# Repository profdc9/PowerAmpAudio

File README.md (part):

# Modified C300 Amplifier

This is a PCB layout by Daniel Marks based on Michael Chua's C300 amplifier which can be found at:

https://www.ampslab.com/c300.htm

This is a project designed to be a good quality amplifier that is achieves good quality distortion (< 0.1% THD at 10 kHz and 300 W per channel max), and is both educational (to study for electronics engineering and hobbyist use) and archival (to be useful long into the future, or "future proofed").  This is a layout from 2020 but it is assumed that decades into the future, relatively few bipolar transistor models will be available as through-hole and discrete component electronics become ever more rare.  Through-hole and discrete devices are currently being phased out from major manufacturers, however, Chinese and other second-source manufacturers are still producing them.  Therefore emphasis with this design has been placed on keeping the design simple with a minimal number of part types and flexible substitution, perhaps at the expense of the performance that could be achieved at using the very best parts available in 2020.  

There are five PCBs in this project:

1.  PowerampC300 - a C300 power amplifier that uses TO220 transistors (BCE layout) as the intermediate power transistors, with the benchmark devices being MJE15032/MJE15033.
2.  PowerampC300TO126 - the same power amplifier that uses TO126 devices (ECB layout), the benchmark devices being MJE340/350.
3.  A power conditioning board (PowerCond) intended to provide clean power to the PCBs and isolate the power between the channels, as well as enable the use of switching power supplies by filtering switching noise.  It may also be used with a conventional unregulated supply (diode bridge and filter capacitors).
4.  A PCB with XLR to unbalanced conversion.  This is currently using a THAT1200 part but can be reconfigured for other types of chips from Analog Devices SSM2131 or Texas Instruments INA134.  
5.  SoftStart - a relay based soft start which supports external triggering mode from an AV receiver.  This PCB prevents current inrush when an unregulated supply with large reservoir capacitors are used.

The small signal transistors are of 2N5401/2N5551 type (though MPSA42/MPSA92 may be substituted, with the THD approximately doubling because of the reduced loop bandwidth as the beta of these transistors is smaller).  Q1/Q2 may be advantageously substituted with MPSA18 if available to decrease the noise at the input.

The power transistors may be of many TO-247 or TO-264 types as available.  The footprints for the power transistors allow for under PCB, over PCB, or surface lead mounting.

There are only three types of transistors that are needed for this project to keep : a small signal, high voltage type (for example 2N5401/2N5551), a medium power type (for example MJE15032/MJE15033 or MJE340/MJE350), and a high power output stage type (for example MJL3281A/MJL1302A).

The original design calls for mica capacitors for C9 and C6.  C6 generally is not needed and can be left open, but 10 pF maximum should be used for a small amount of phase lead if required.  A good choice for C9 is 100 pF which should provide reasonable stability for a wide variety of transistor types.  As silver mica capacitors are becoming more rare, C0G/NP0 capacitors with 1 kV minimum voltage may be substituted in a pinch.  Most of the other capacitors of 0.1 uF size are either polypropylene film capacitors (7.5 to 10 mm footprint) or ceramic disc type (5 mm footprint).  As polystyrene capacitors are already exceedingly rare in 2020, the best substitute is likely to be polypropylene capacitors.  In particular, X7R/Y5V types use a ferroelectric dielectric and therefore are "microphonic" in that the sound will be converted to a small voltage by these capacitors, in a manner similar to that of an electret microphone, and therefore these should be avoided except in a handful of places where their influence is minimized.

C1 is a 10 uF decoupling polyethylene film capacitor.  It is fairly large.  Should it not be available, something like two 22 uF, 100 to 250V (larger the better) electrolytics can be used, wired in series with negative terminals joined.  Electrolytics, however, have somewhat higher distortion than film capacitors.

Resistors should be of metal-film types, except R33-R40 which may be wirewound.

THe inductor L1 is an output inductor intended to improve stability for highly capacitive loads (e.g. electrostatic speakers).  It may be a coil of 16-18 gauge magnet wire, 10 turns and 25 mm diameter.

All of the gerbers are available as well as the Kicad files, which is an open-source PCB layout program.  The PCBs are two-layer boards.  Modelling of the amplifier (both open-loop and distortion) has been performed with Qucs-S/ngspice with these simulation files included.

# WARNINGS

This project involves high voltages, high currents, and high power.  You must take proper precaution to prevent injury or death from electrocution.  The voltages and currents could cause excessive heating or electrical fires.  You must take proper precautions to properly ground equipment, especially mains voltages, so that these do not come in contact with the chassis possibly cause electrocution.  The chassis of the equipment should be attached to earth ground with proper fusing.  Large amounts of energy may be stored in capacitors.  If this energy is suddently discharged, for example from accidentally shorting the terminals, injury may result, and the capacitor may be damaged or explode.  Wiring electrolytic capacitors in reverse polarity is likely to cause damage or explosion.  This list of potential dangers is not exhaustive; you assume all risk.

# Part substitutions

## Transistors

The small signal transistors are chosen to be 2N5551 (NPN) and 2N5401 (PNP).  These should have Vcemax of at least 150 V, minimum collector current 100 mA, hFE at least 100, and gain-bandwidth product 100 MHz or greater.  MPSA42 (NPN) and MPSA92 (PNP) may be subsituted for 2N5551/2N5401, however, these have reduced gain so that the loop gain is reduced and the distortion is somewhat increased.

Because the lead order of TO-126 transistors (ECB) is the opposite of the lead order for TO-220 transistors, TO-126 made be substituted for TO-220 (and vice versa) as long as the device is placed reversed in the PCB (pin 1 and pin 3, and pin 3 at pin 1).  This can not be done with the driver transistors Q15/Q16 because these are against the heat sink and therefore can not be reversed in place.  Therefore, if one wishes to use TO-220 driver transistors but TO-126 VAS transistors, one should use the PowerampC300 project (and not the PowerampC300TO126 project) so that the driver transistors will be oriented correctly to be placed against the heatsink.

The VAS transistors (Q10 and Q12) should have Vcemax at least 200 V, minimum collector current 100 mA, hFE at least 70 (more the better), and gain-bandwidth product at least 15 MHz.  Suitable devices are:

TO-220:  MJE15032 (NPN), MJE15033 (PNP), 3DA4793 (NPN), 3CA1387 (PNP)

TO-126:  MJE340 (NPN), MJE350 (PNP), 2SC3503 (NPN), 2SA1381 (PNP)

The bias servo transistor doesn't need to be anything special should have Vcemax at least 200 V.  Suitable devices are the same types used for the VAS transistors.  

The driver transistors should have Vcemax at least 200 V, minimum collector current 1 A, hFE at least 50, and gain-bandwidth product at least 15 MHz.  Suitable devices are:

TO-220:  MJE15032 (NPN), MJE15033 (PNP), 3DA4793 (NPN), 3CA1387 (PNP)

TO-126:  MJE340 (NPN), MJE350 (PNP)

The output transistors are TO-247/TO-264/TO-3P type.  They should have Vcemax at least 200 V, minimum collector current 15 A, hFE at least 50, and power dissipation at 25 C at least 150 W.  Suitable types include:

MJL3281A (NPN) / MJL1302A (PNP)  TO-264

MJL3281W (NPN) / MJL1302W (PNP)  TO-247

NJW0281 (NPN) / NJW0302 (PNP) TO-3P

2SC5200 (NPN) / 2SA1943 (PNP) TO-264

MJL21194 (NPN) / MJL21193 (PNP) TO-264

MJW21194 (NPN) / MJW21193 (PNP) TO-247

There are known to be versions of the MJL15032, MJL15032, NJW0281, NJW0302 available from by Chinese vendors (search lcsc.com).  These may have sufficient performance for creating lower cost implementations of the amplifier. 

## Power terminals

The power terminals are designed to take the common 5.0/5.08 mm spaced screw terminal blocks.  Alternatively, 6.35 mm male spade terminals with 5.0 mm pitch pins may be soldered into the board.  Screw terminal blocks are easier to swap out but are not as secure, while spade terminals can be quite secure but sometimes difficult to remove if required.

## Audio connectors

To connect unbalanced audio to the amplifier PCBs and to the balanced to unbalanced PCBs, either two wires or a SMA cable may be used.  A SMA cable has the advantage of inherent shielding.  If a SMA cable is wired to an input unbalanced RCA jack, the jack should be an isolated jack with the ring of the jack wired to the input star ground where the chassis earth ground is.

## Balanced to unbalanced differential line receiver

The balanced to unbalanced PCB can be set up to preferentially use the THAT1200, but also can be configured for the THAT1240, INA134, or SSM2141.

# Building the amplifier (PowerampC300 and PowerampC300TO126)

The PCB is two-sided without any links with all components soldered to the top side.  Populate the small components first (transistors, resistors, small capacitors).  Leave the larger components such as C1, Q10, Q11, Q12, Q15, Q16, the driver transistors Q17-Q24 for later as they will make the PCB more unwieldy to work with.

Q10 and Q12 should be mounted to small vertical heatsinks sufficient of dissipating 10 W.  An insulating silicone pad or mica sheet should be placed between the collector tab and the heatsink so that the heatsink is not electrically connected to the transistor.  A bushing should be used on TO-220 types of insulate the mounting screw from the heatsink.

Q15, Q16, and Q17-Q24 are all mounted in a row to a heatsink.  There is a file "Drillpattern.pdf" which shows the position of the holes on the heatsink for the transistors which can be taped over the heatsink to mark the positions to tap.  All of these transistors should have silicone pads or mica sheets insulating the collector tabs from the heatsink.  AFTER INSTALLATION, THE HEATSINK SHOULD BE CAREFULLY CHECKED WITH A MULTIMETER TO MAKE SURE THERE IS NO CONTINUITY BETWEEN THE COLLECTORS (middle pin) OF ANY OF THE TRANSISTORS AND THE HEATSINK.  For an aluminum heatsink, M3 (metric) or 4-40 (SAE) holes may be tapped in the heatsink to mount the transistors.  After tapping, there is likely to be burrs from the tapping process, so sanding the heatsink with the a fine sandpaper is often require to remove these burrs.  These burrs may poke through a silicone pad or mica sheet and contact the transistor causing a potentially catastrophic short circuit.  If Q15 and Q16 are TO-220 transistors, a bushing should also be used to insulate the tab from the mounting screw.  It is helpful when installing the transistors to gently curl the legs away from the heatsink slightly so that they can be easily bent if a little persuasion is needed to make the position of the transistor mounting hole reach the tapped hole.  

A hole should be tapped on the heatsink above Q15 and Q16 to place the bias servo transistor Q11.  The three legs of Q11 are soldered to extension wires, and heat shrink tubing is applied to the extension wires to prevent inadvertent contact the between the wires or to the heatsink.  The other end of the wires are soldered into the PCB at the Q11 position so that Q11 is tethered to the PCB but may freely moved.  Q11 can be mounted to the heatsink similarly to how Q15 and Q16 are, using an insulating silicone or mica pad and a bushing if required.  Again, check to make sure there is no continuity between the heatsink and the collector of Q11.

The heatsink may be mounted with the transistors laying flat parallel to the PCB, or the heatsink stood upright so the transistors are sticking up from the PCB.  Which one is used depends on the case mounting and heatsink type.

After assembly carefully inspect the PCB front and back, especially solder pads for any accidental bridges or incomplete or cold solder joints.  A lighted magnifier is very helpful for this.  If joints are not being properly made, it could be because the solder is old and has bad flux or the board was not clean before starting.  This is particularly troublesome to make reliable solder joints, and fresh flux should be applied to ensure joints are properly wetted.

CONNECT THE POSITIVE SUPPLY LEADS (GND/V+) to the PCB before the negative supply leads (V-/GND).  If there is only a negative supply attached to the amplifier PCB, the amplifier may be damaged (transistors Q8 or Q9).  Before powering, the DC offset control trimmer R10 should be set to the middle position in resistance (approximately 50 ohms between wiper and contacts), and bias control trimmer R22 should be to maximum resistance (200 ohms).  

The file "Grounding.pdf" shows a diagram of how to connect the amplifier to minimize ground loops.  Pay attention to isolate the jacks from the chassis, twist the conductors of the power together, twist the conductors of the output cables together, and bond the input jacks together and possibly to one point on the chassis.

Powering up for the first time is always a nerve-racking experience.  All power connections from the transformer to the power conditioning PCB to the amplifier PCB should be thoroughly checked to ensure that both supplies are properly connected.  The best approach is to use an isolated variac with a AC current meter to power the amplifier so that the voltage may be slowly increased and it can be seen if any excessive currents are encountered.  However, if a variac is not available, one may be able to place 220 ohm, 5 watt resistors in series with the positive and negative rails so that when one initially powers on, the full current available from the power supply does not cause excessive damage to the PCB if there is a problem.  

The amplifier should first be powered up without a load.  If there is a faulty component or faulty connections, such as unreliable power connections, the amplifier may oscillate.  This sometimes often results in the destruction of Q8, and occasionally R19 and R24.  Damage to the resistors is usually obvious and can easily be tested in circuit.  Q8 can still measure properly with a diode checker in circuit but be faulty.  Therefore one should replace Q8 if there is any doubt if it is functioning correctly.

Once the amplifier has operated at full voltage without a load, a dummy load should be attached to the amplifier output.  A dummy load can be constructed, for example, from many smaller 8-ohm, 5 W sandblock or metal-oxide resistors.  For example, thirty six of these resistors, with 6 strings of resistors in parallel, each string being 6 resistors in series, makes a convenient 180 watt, 8 ohm audio load.  

The quiescent current of the class AB stage should be set.  Trimmer R22 controls the voltage bias between the bases of the NPN and PNP transistors and therefore the quiescent current.  By decreasing the resistance of R22, the quiescent current is increased.  The quiescent current of an output transistor may be measured using the voltage between the emitter of the transistor and the output of the amplifier.  With R22 at maximum resistance, this should be very close to 0 mV.  Slowly decrease the resistance of R22, measuring the increase of the voltage.  Because the voltage is across the output 0.39 ohm resistor, to achieve 35 mA quiescent current, 14 mV should be measured.  Because of differences between transistors, the quiescent currents in different transistors are likely to be slightly different.  Try to ensure that no output transistor has excessive current, perhaps exceeding 60 mA.  

Without any input to the amplifier, when the amplifier is powered up, the DC voltage measured across the 8 ohm audio load should read very close to zero, within 100 mV at most.  Trimmer R10 should be adjusted to reduce the DC offset at the output to below 10 mV.  

With the quiescent current and output DC offset adjusted, you can apply a signal to the amp.  Use an oscilloscope to measure the voltage on the audio load.  Inject a sine wave input signal into the amplifier of about 1000 Hz and 0.1 V peak.  Because the gain of the amplifier is approximately 31, this should result in a 3.1 V output on the audio load.  The signal can be generated either by a signal generator, or by a computer sound card which is input into a preamplifier.  Turn the preamplifier down and adjust the input signal amplitude.  A very clean sine wave output should be observed.

Slowly increase the amplitude of the sine wave, up to perhaps 1.0 V, so that the peak output voltage is 31 V.  A clean sine wave should still be observed.  The audio load will start to get hot, so keep the audio load on a surface (for example a ceramic dish) to insulate it from the table.  

Next, change the output from a sine wave to a square wave at 20 kHz.  A nice, clean square wave should be observed with little or no ringing.  The rise/fall time on the square wave should be about 2 microseconds or so.

Once you are confident that the amplifier is stable, you can try your (not best) speaker with it.  A pure tone should be heard without distortion.  If you are hearing hum, you may have a problem with grounding inside the amplifier or a ground loop.  If you short the input to the amplifier, and still hear hum, the problem is inside the amplifier.  Check to see that the amplifier is grounded at the input jacks (and only there) to the earth ground connection on the chassis.  If not in the amplifier, you may need to investigate if the device generating the signal has multiple ground connections inside it.

After all of this, you should be good to go.  Be careful as the amplifier has a lot of power and can damage speakers not rated for the full power.

# Building the power conditioning board

The power conditioning board is not strictly required.  However, it serves three functions.  It rectifies AC to DC when an unregulated transformer supply is used.  It serves to filter out RF noise and brief voltage spikes from the diode commutation from the amplifier, as well as any other noise coming from the mains.  The filtering is also useful is one uses switching power supplies rather than an unregulated transformer supply to filter the switching noise.  Finally, it serves as a terminal block to connect the reservoir capacitors and amplifier.  Typically, one power conditioning board is used per channel.

The common mode chokes can be constructed by hand.  Four are required for each power conditioning board.   Typically, small ferrite toroids are obtained, usually between 16 to 25 mm in outer diameter.   Small green cores available widely on sites like ebay, Amazon, or aliexpress are suitable.  The primary and secondary turns are two different colors of 18 AWG (1 mm diameter) solid copper wire.  The two wires are wound together side-by-side through the core five or six times.  When soldering the core into the PCB, the silkscreening shows how the wires are connected.  The same color wire is soldered to both pads connected by the line in the silkscreen.  The same ends of the two wires are soldered to the two pads next to each other on the same side of the PCB.  Solder should be applied to both the top side and bottom side of the pad to ensure the wire is held solidly.

The mounting holes at the corners of the PCB are intended to be grounded to the case through standoffs to shunt the filtered RF noise signal to the case.  

# Building the SoftStart board

The SoftStart board is relatively straightforward to build.  Special attention should be paid to acquiring X2 capacitors for C1 and C2.  The extra non-plated through holes in the PCB are so that the mains and switch wires soldered to the PCB can be threaded through the PCB and collared with a cable tie as a strain relief so that it does not pull out of the PCB.  The cable tie will prevent stress from being applied to the solder joint on the PCB.  Generally, a cover should be placed over the back side of the PCB (for example a polycarbonate sheet) to prevent contact of the solder joints with the case.  It is highly recommend to put heat shrink tubing over any exposed mains connections, for example, at the power entry panel, switch or fuse holder.  

Depending on the size of the reservoir capacitors in your amplifier, it may be necessary to change the 150 ohm resistors to a smaller value and allow a somewhat larger charging current before the resistors are bypassed by the relay.  This depends on the peak current that is permitted.

# Building the XLR to Unbalanced board

This board uses the THAT1200 balanced line receiver to transform the signal from a balanced XLR connector to an unbalanced signal.  The unbalanced signal may be connected from the XLR to Unbalanced board to the amplifier board with a shielded SMA cable to prevent noise pickup.  If the THAT1200 is not available, the THAT1240, INA134, or SSM2141 balanced line receivers may be used.  In this case, C5 and C17 should be omitted and JP1 and JP2 are shorted.

The transistors Q1 and Q2 should have heatsinks attached and fitted with pads and bushings to electrically isolate the heatsink from the collector.  J12 is a ground terminal block from which a grounding wire and lug may be extended to the common input grounding point on the chassis of the amplifier.

# Different types of feedback

There are three kinds of feedback that can be customized to provide a tradeoff of distortion vs. loop stability.  Some audiophiles like to attain the minimum distortion.  It is likely that the distortion is sufficiently low, especially at power levels significantly below the maximum power, that distortion is not likely to be noticed.  It is highly recommended when using compensation methods that could be more unstable that the inductor L1 is installed, as any significant capacitive loading is likely to cause oscillation.

For the audiophile true believers, three feedback options are provided: Conventional Miller Compensation (CMC), Two-Pole Compensation (TPC), and Output Inclusive Two-Pole Compensation (OITPC).  Small value capacitors are ideally silver mica type (470 pF or less), but NP0/C0G types can work as well.  The 100 nF are polypropylene film capacitors, 100 V or more.

## Conventional Miller Compensation (CMC)
As shown, the circuit is configured for CMC.  In this case, C9=150 pF, C3=150 pF, C25 is a shorting wire, R18, C20, and C24 are not included.  For slightly less distortion, C9=100 pF and C3=100 pF. 

## Two-Pole Compensation (TPC)
To configure for Two-Pole Compensation, C3 and C20 are not included, C9 and C25 are 220 pF, R18 is 2k2, and C24 is 100 nF.  Simulations suggest that at mid range frequencies, distortion can be decreased by 14 dB, and at 10 kHz by 8 dB.

## Output Inclusive Two-Pole Compensation (OITPC)
OITPC is a relatively new option that is included for study and experimentation.  To configure for OITPC, C9 and C25 are 100 pF, R18 is 390 ohms, C20 is 100 pF, and C24 is 100 nF, C3 is not included.  

# A brief explanation of the operation of the amplifier
The amplifier is a class AB configuration with approximately 34 dB of gain and employing global negative feedback, as well as local feedback in the form of compensation.

Capacitor C1 is a film capacitor that isolates DC from the input but passes frequencies above 2-3 Hz.  Q1 and Q2 are a differential pair for which the error feedback signal is the current through the collector of Q1.  

R6, R7, R8, R9, and R10 are used to null any DC offset on the output, with the potentiometer R10 fine-tuning the DC offset.  Q7 is a constant current source with a fixed voltage between its base and emitter which is determined by the red LED.  The emitter resistor R12 sets the current at approximately (LED voltage=2.0 V - 0.7 VBE) / R12.  The same LED also sets the voltage on the emitter of Q12 which is likewise a constant current source for the VAS (voltage amplification stage).

Q5 and Q6 have their bases joined together and fixed at a voltage 33 V above ground so that their emitters are fixed at one diode drop below the bases.  This is a cascode configuration that holds the collectors of Q1/Q2 at a constant voltage as to reduce the Miller effect.  This is also helpful to limit the VCE of Q1 and Q2 in case a low voltage transistor such as MPSA18 is used, which has a maximum VCE of 45 V.

Q3 and Q4 are a current mirror forming a high impedance load for the differential pair so that high gain is achieved.  The output impedance of Q3 is limited by the Early effect which can be at quite a high voltage for a high voltage transistor such as 2N5401.  R5 and C3 form a high-pass network which serves to help increase the phase margin at high frequencies by reducing the open loop gain at high frequencies.

Because Q3 acts as a high impedance load, the current from Q1 is steered into the base of Q8 which is an emitter-follower configuration.  This minimizes the load of Q1.  Q8 is a vulnerable transistor as it drives Q10 with whatever current is necessary to maintain feedback, even when the amplifier is at the rails.  To prevent the current in the collector of Q8 from exceeding safe operating limits, transistor Q9 steals base current from Q8 when the current in the VAS exceeds about 20 mA.  This is one diode drop across the emitter-base of Q9 divided by resistor R19.  If Q9 is not present a brief excursion into the rails can destroy Q8 as the voltage and current on it can greatly exceed tolerable limits.

Q10 and Q12 are a conventional one-sided VAS arrangement, with Q12 being a constant current source of about 11 mA, and Q10 being a common-emitter configuration.  This produces a second high gain stage, which when combined with the gain of the differential pair, produces the needed open loop gain in the amplifier.

With C9 at 100-150 pF and C25 short circuited, this amplifier employs conventional Miller compensation.  This is a negative feedback arrangement that introduces a pole into the open loop gain of the amplifier.  It is the main mechanism stabilizing the amplifier.  The pole ensures that any other poles in the amplifier due to limited component bandwidth occur with a gain margin of 10 dB or greater.  By including a capacitor at C20, the compensation includes the output signal and partially compensates for the relatively slow speed of the output transistors.

Transistor Q11 is in a "rubber diode" configuration that is an adjustable fixed bias to achieve a quiescent current in the output transistors Q17 to Q24.  The voltage differences between the bases Q17, Q19, Q21, and Q23 and Q18, Q20, Q22, and Q24 determine the quiescent current.  More quiescent current generally reduces crossover distortion but dissipates more constant power.  Potentiometer R22 is used to adjust the quiescent current, which is typically about 10 to 15 mA per output transistor, and is typically measured across the resistors R33-R40. 

D13 and D14 are catch diodes that limit the output current at very high current output.  When the diodes are forward biased, VAS current is diverted directly to the output, limiting the base current of Q13 and Q14 and therefore output current of the amplifier.

Q13 and Q14 are a V-I limiter which limits the output current when the impedance of the load drops below 2 ohms.  The voltage is sensed on the emitter resistors R39 and R40.  This is reduced by the divider networks R26/R29 and R27/R30.  When the emitter-base voltage on Q13 or Q14 exceeds one diode drop, or about 0.6 V, the transistors start to steal base current from Q15/Q16 which limits the output current.  This acts as a temporary protection for the output transistors to keep them within the safe operating area.  However, it is recommended to use a fuse on the power supply as well so that in case of a prolonged short circuit, the fuse blows.

Q15/Q16 and the output transistors Q17-Q24 form a conventional Darlington class AB stage.  As the VAS can source a maximum of about 10 mA, the hFE of Q15/Q16 is about 50, and the hFE of Q17-Q24 is about 50, the maximum current is on the order of 15 to 25 A, which corresponds to a very high peak power.  However, four transistors are needed as the thermal load is shared between them, and dividing the current load between them ensures they are kept within the SOA.  It is recommended that if 2SC5200/2SA1943 transistors are used, the maximum supply voltage is limited to 50 to 55 V as the SOA of these transistors is somewhat less than the MJL3281A/MJL1302A which can handle up to 70 V.

R52 and U1 are yet another optional feature to protect the amplifier.  When the output current exceeds 8 A, the optotriac U1 LED turns on which triggers the triac.  This short circuits the bias at the output so that the catch diodes D13 and D14 divert the VAS current into the output and the output is mostly turned off.  The output remains off until the power is cycled.  This feature may be needed for those that torture and damage the amplifier regularly, but is probably not needed for ordinary use.

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
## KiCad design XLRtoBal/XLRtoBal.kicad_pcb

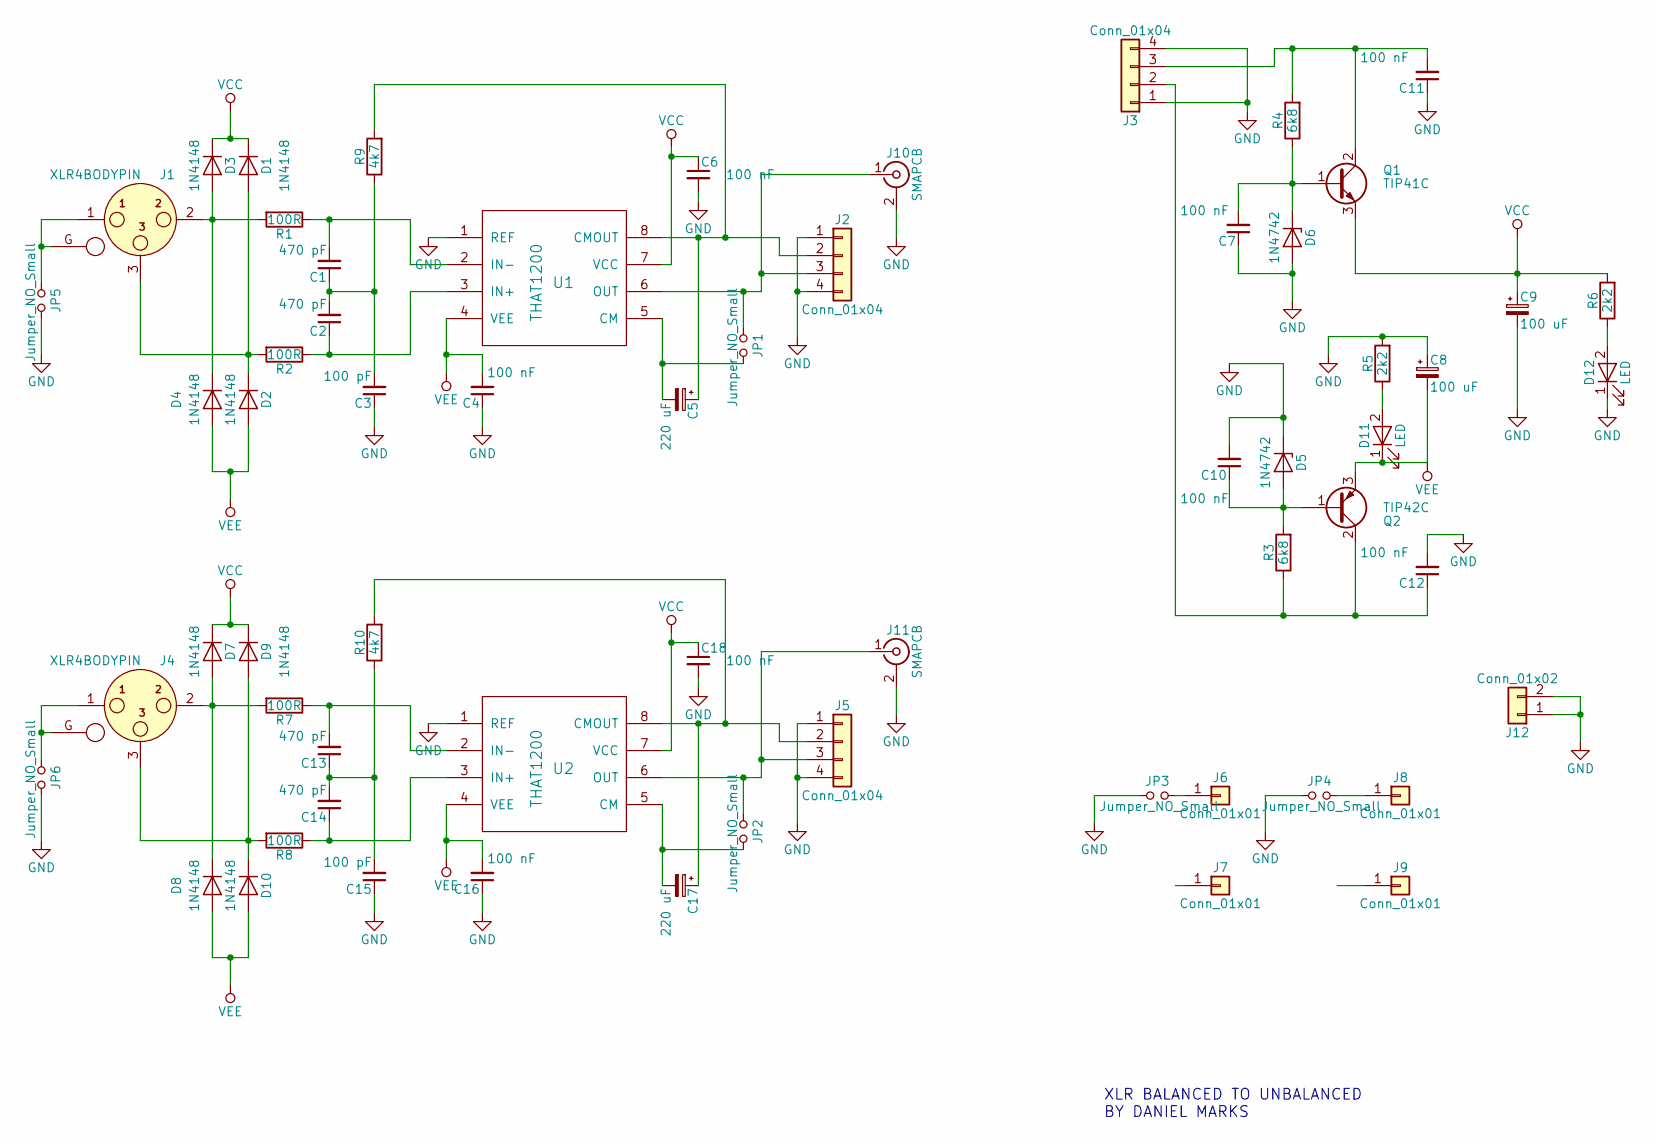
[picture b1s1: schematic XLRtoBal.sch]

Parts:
C1, C2, C13, C14: 470 pF; C_Disc_D5.0mm_W2.5mm_P5.00mm; LCSC C263196
C3, C15: 100 pF; C_Disc_D5.0mm_W2.5mm_P5.00mm; LCSC C400081
C4, C6, C7, C10, C11, C12, C16, C18: 100 nF; C_Disc_D5.0mm_W2.5mm_P5.00mm; LCSC C454377
C5, C17: 220 uF; CP_Radial_D8.0mm_P5.00mm; LCSC C239308
C8, C9: 100 uF; CP_Radial_D10.0mm_P5.00mm; LCSC C125770
D1, D2, D3, D4, D7, D8, D9, D10: 1N4148; D_DO-35_SOD27_P7.62mm_Horizontal; LCSC C14516
D5, D6: 1N4742; D_DO-41_SOD81_P7.62mm_Horizontal; LCSC C36751
D11, D12: LED; LED_D3.0mm
J1, J4: XLR4BODYPIN
J2, J5: Conn_01x04; TerminalBlock_bornier-4_P5.08mm; LCSC C395849
J3: Conn_01x04; TerminalBlock_bornier-4_P5.08mm_with_spade; LCSC C395849
J6, J7, J8, J9: Conn_01x01; 1pin
J10, J11: SMAPCB; SMA_THT_Jack_Straight; LCSC C496549
J12: Conn_01x02; TerminalBlock_bornier-2_P5.08mm_with_spade
JP1, JP2, JP3, JP4, JP5, JP6: Jumper_NO_Small; Pin_Header_Straight_1x02_Pitch2.54mm
Q1: TIP41C; TO-220-3_Vertical; LCSC C358526
Q2: TIP42C; TO-220-3_Vertical; LCSC C358527
R1, R2, R7, R8: 100R; R_Axial_DIN0207_L6.3mm_D2.5mm_P7.62mm_Horizontal; LCSC C57438
R3, R4: 6k8; R_Axial_DIN0309_L9.0mm_D3.2mm_P12.70mm_Horizontal; LCSC C176446
R5, R6: 2k2; R_Axial_DIN0207_L6.3mm_D2.5mm_P7.62mm_Horizontal; LCSC C58595
R9, R10: 4k7; R_Axial_DIN0207_L6.3mm_D2.5mm_P7.62mm_Horizontal; LCSC C57438
U1, U2: THAT1200; DIP-8_W7.62mm_Socket; LCSC C115171

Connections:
GND: C3.1, C4.1, C6.2, C7.1, C8.1, C9.2, C10.2, C11.1, C12.2, C15.1, C16.1, C18.2, D5.1 (K), D6.2 (A), D12.1 (K), J2.1, J2.4, J3.1, J3.4, J5.1, J5.4, J10.2 (Ext), J11.2 (Ext), J12.1, J12.2, JP3.1, JP4.1, JP5.2, JP6.2, R5.2, U1.1 (REF), U2.1 (REF)
unnamed: C1.1, C2.2, C3.2, R9.1
unnamed: C1.2, R1.1, U1.2 (IN-)
unnamed: C2.1, R2.1, U1.3 (IN+)
unnamed: C5.1, J2.2, R9.2, U1.8 (CMOUT)
unnamed: C5.2, JP1.2, U1.5 (CM)
unnamed: C7.2, D6.1 (K), Q1.1 (B), R4.1
unnamed: C10.1, D5.2 (A), Q2.1 (B), R3.2
unnamed: C11.2, J3.3, Q1.2 (C), R4.2
unnamed: C12.1, J3.2, Q2.2 (C), R3.1
unnamed: C13.1, C14.2, C15.2, R10.1
unnamed: C13.2, R7.1, U2.2 (IN-)
unnamed: C14.1, R8.1, U2.3 (IN+)
unnamed: C17.1, J5.2, R10.2, U2.8 (CMOUT)
unnamed: C17.2, JP2.2, U2.5 (CM)
unnamed: D1.2 (A), D2.1 (K), J1.3, R2.2
unnamed: D3.2 (A), D4.1 (K), J1.2, R1.2
unnamed: D7.2 (A), D8.1 (K), J4.2, R7.2
unnamed: D9.2 (A), D10.1 (K), J4.3, R8.2
unnamed: D11.2 (A), R5.1
unnamed: D12.2 (A), R6.1
unnamed: J1.1, J1.G, JP5.1
unnamed: J4.1, J4.G, JP6.1
unnamed: J6.1, JP3.2
unnamed: J8.1, JP4.2
unnamed: J2.3, J10.1 (In), JP1.1, U1.6 (OUT)
unnamed: J5.3, J11.1 (In), JP2.1, U2.6 (OUT)
VCC: C6.1, C9.1, C18.1, D1.1 (K), D3.1 (K), D7.1 (K), D9.1 (K), Q1.3 (E), R6.2, U1.7 (VCC), U2.7 (VCC)
VEE: C4.2, C8.2, C16.2, D2.2 (A), D4.2 (A), D8.2 (A), D10.2 (A), D11.1 (K), Q2.3 (E), U1.4 (VEE), U2.4 (VEE)

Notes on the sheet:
XLR BALANCED TO UNBALANCED BY DANIEL MARKS

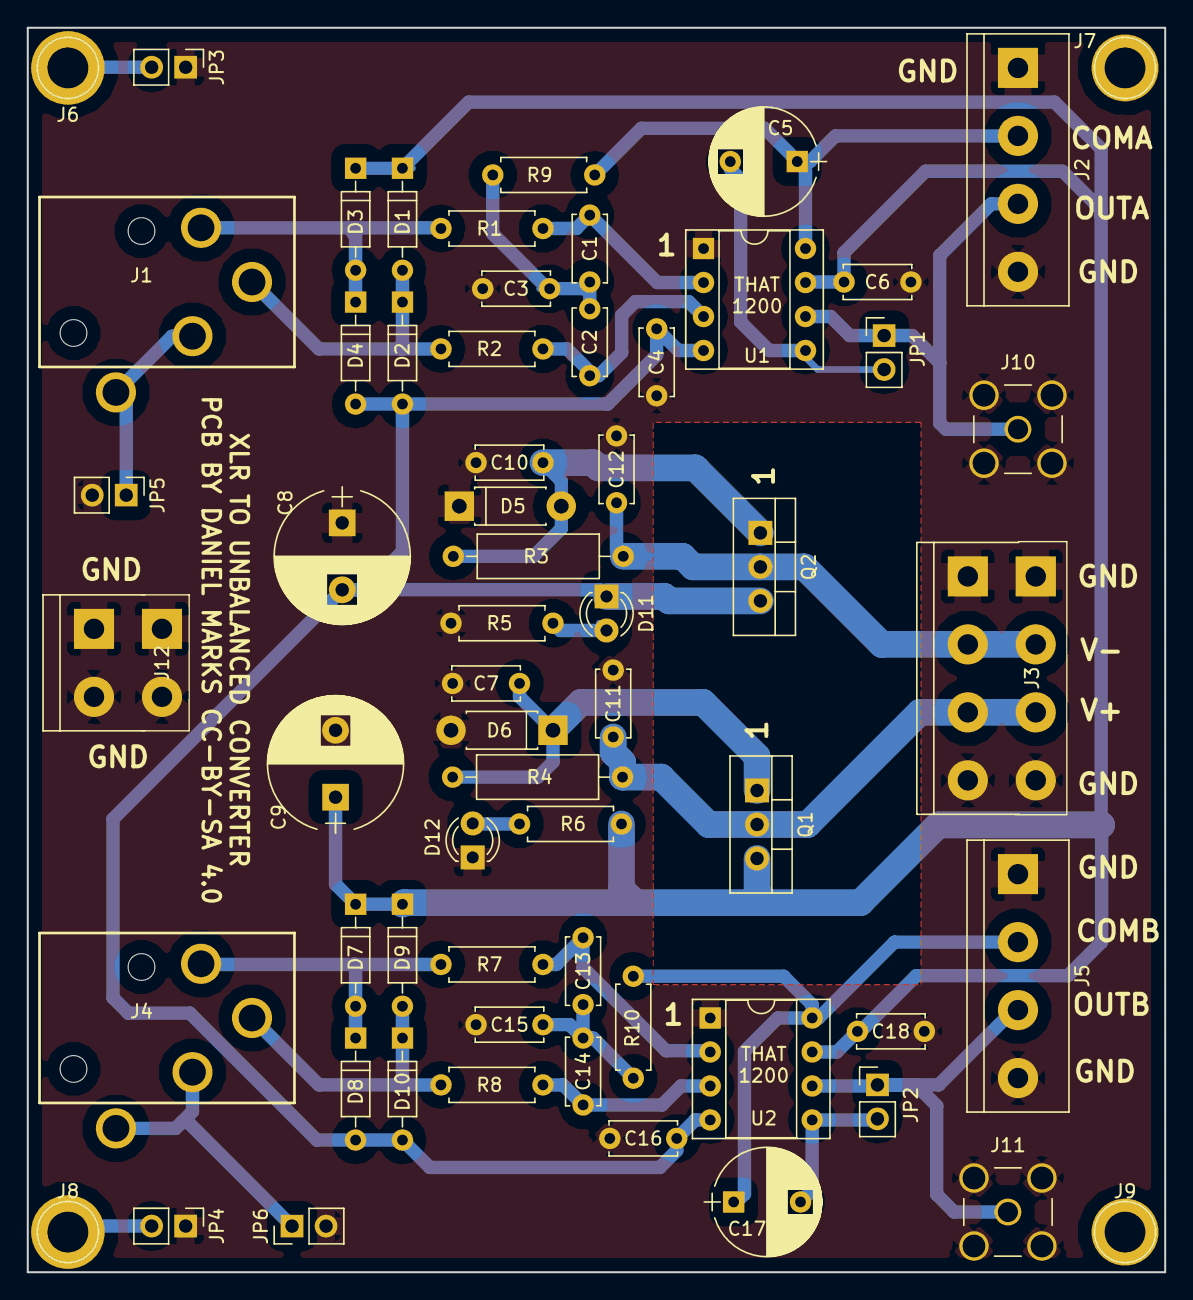
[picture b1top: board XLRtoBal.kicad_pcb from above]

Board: 2 copper layers, 85.0 x 93.0 mm, 62 parts (0 on the bottom side), 29 nets.

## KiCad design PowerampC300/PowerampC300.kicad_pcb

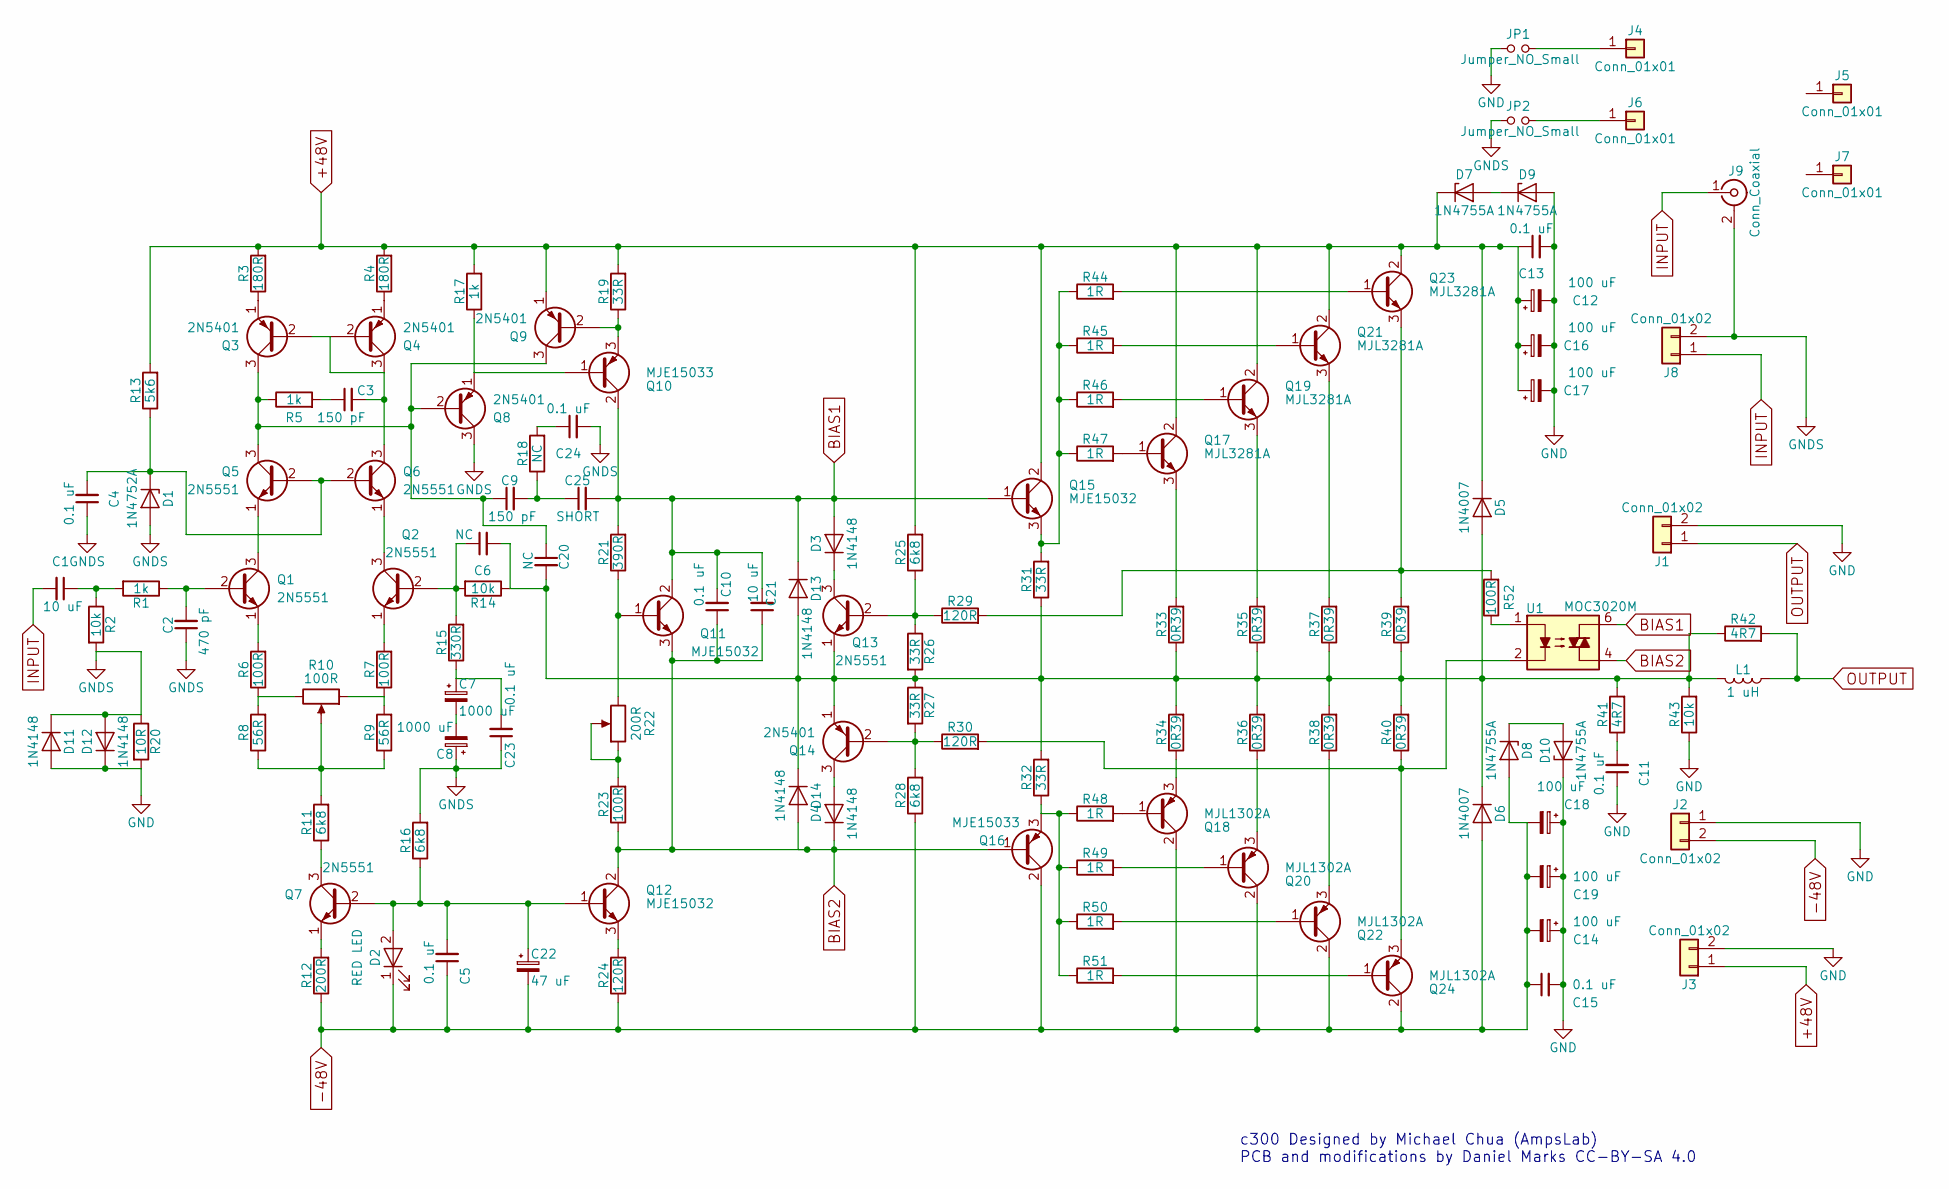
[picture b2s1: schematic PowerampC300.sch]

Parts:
C1: 10 uF; C_Rect_L16.5mm_W5.0mm_P15.00mm_MKT; LCSC C328801
C2: 470 pF; C_Rect_L7.0mm_W3.5mm_P5.00mm; LCSC C328872
C3: 150 pF; C_Axial_L3.8mm_D2.6mm_P7.50mm_Horizontal; LCSC C434407
C4, C5: 0.1 uF; C_Disc_D5.0mm_W2.5mm_P5.00mm; LCSC C454377
C6: NC; C_Disc_D5.0mm_W2.5mm_P5.00mm; LCSC C342428
C7, C8: 1000 uF; CP_Radial_D10.0mm_P5.00mm; LCSC C88750
C9: 150 pF; C_Disc_D5.0mm_W2.5mm_P5.00mm; LCSC C366798
C10, C11, C13, C15, C23, C24: 0.1 uF; C_Axial_L3.8mm_D2.6mm_P10.00mm_Horizontal; LCSC C390130
C12, C14, C16, C17, C18, C19: 100 uF; CP_Radial_D14.0mm_P7.50mm; LCSC C330940
C20: NC; C_Disc_D5.0mm_W2.5mm_P5.00mm; LCSC C366798
C21: 10 uF; C_Disc_D5.0mm_W2.5mm_P5.00mm; LCSC C454377
C22: 47 uF; CP_Radial_D5.0mm_P2.50mm; LCSC C88750
C25: SHORT; C_Disc_D5.0mm_W2.5mm_P5.00mm; LCSC C366798
D1: 1N4752A; D_DO-41_SOD81_P7.62mm_Horizontal; LCSC C2555
D2: RED LED; LED_D3.0mm; LCSC C99771
D3, D4, D11, D12, D13, D14: 1N4148; D_DO-35_SOD27_P7.62mm_Horizontal; LCSC C125770
D5, D6: 1N4007; D_DO-41_SOD81_P7.62mm_Horizontal; LCSC C193790
D7, D8, D9, D10: 1N4755A; D_DO-41_SOD81_P7.62mm_Horizontal
J1, J2, J3: Conn_01x02; TerminalBlock_bornier-2_P5.08mm_with_spade; LCSC C395849
J4, J5, J6, J7: Conn_01x01; 1pin
J8: Conn_01x02; TerminalBlock_bornier-2_P5.08mm; LCSC C395849
J9: Conn_Coaxial; SMA_THT_Jack_Straight; LCSC C496549
JP1, JP2: Jumper_NO_Small; Pin_Header_Straight_1x02_Pitch2.54mm
L1: 1 uH; L_Radial_D16.8mm_P11.43mm_Vishay_IHB-1
Q1, Q2, Q5, Q6, Q7, Q13: 2N5551; TO-92_Inline_Wide
Q3, Q4, Q8, Q9, Q14: 2N5401; TO-92_Inline_Wide
Q10, Q16: MJE15033; TO-220-3_Vertical
Q11, Q12, Q15: MJE15032; TO-220-3_Vertical
Q17, Q19, Q23: MJL3281A; TO-264_Vertical_w_pads; LCSC C327498
Q18, Q20, Q22, Q24: MJL1302A; TO-264_Vertical_w_pads; LCSC C327497
Q21: MJL3281A; TO-264_Vertical_w_pads; LCSC' C327498
R1, R17: 1k; R_Axial_DIN0207_L6.3mm_D2.5mm_P7.62mm_Horizontal; LCSC C57435
R2, R14: 10k; R_Axial_DIN0207_L6.3mm_D2.5mm_P7.62mm_Horizontal; LCSC C57436
R3, R4: 180R; R_Axial_DIN0207_L6.3mm_D2.5mm_P7.62mm_Horizontal; LCSC C172976
R5: 1k; R_Axial_DIN0207_L6.3mm_D2.5mm_P7.62mm_Horizontal; LCSC C173036
R6, R7: 100R; R_Axial_DIN0207_L6.3mm_D2.5mm_P7.62mm_Horizontal; LCSC C172966
R8, R9: 56R; R_Axial_DIN0207_L6.3mm_D2.5mm_P7.62mm_Horizontal; LCSC C119298
R10: 100R; Potentiometer_Trimmer_Bourns_3296W; LCSC C83688
R11: 6k8; R_Axial_DIN0411_L9.9mm_D3.6mm_P12.70mm_Horizontal; LCSC C176446
R12: 200R; R_Axial_DIN0207_L6.3mm_D2.5mm_P7.62mm_Horizontal; LCSC C58613
R13: 5k6; R_Axial_DIN0411_L9.9mm_D3.6mm_P12.70mm_Horizontal; LCSC C138185
R15: 330R; R_Axial_DIN0207_L6.3mm_D2.5mm_P7.62mm_Horizontal; LCSC C58608
R16: 6k8; R_Axial_DIN0309_L9.0mm_D3.2mm_P12.70mm_Horizontal; LCSC C176446
R18: NC; R_Axial_DIN0207_L6.3mm_D2.5mm_P7.62mm_Horizontal; LCSC C173010
R19: 33R; R_Axial_DIN0309_L9.0mm_D3.2mm_P12.70mm_Horizontal; LCSC C176446
R20: 10R; R_Axial_DIN0207_L6.3mm_D2.5mm_P7.62mm_Horizontal; LCSC C173010
R21: 390R; R_Axial_DIN0207_L6.3mm_D2.5mm_P7.62mm_Horizontal; LCSC C173010
R22: 200R; Potentiometer_Trimmer_Bourns_3296W; LCSC C83685
R23: 100R; R_Axial_DIN0207_L6.3mm_D2.5mm_P7.62mm_Horizontal; LCSC C172973
R24: 120R; R_Axial_DIN0207_L6.3mm_D2.5mm_P7.62mm_Horizontal; LCSC C119298
R25, R28: 6k8; R_Axial_DIN0411_L9.9mm_D3.6mm_P15.24mm_Horizontal; LCSC C138189
R26, R27: 33R; R_Axial_DIN0207_L6.3mm_D2.5mm_P7.62mm_Horizontal; LCSC C173006
R29, R30: 120R; R_Axial_DIN0207_L6.3mm_D2.5mm_P7.62mm_Horizontal; LCSC C172969
R31, R32: 33R; R_Axial_DIN0411_L9.9mm_D3.6mm_P12.70mm_Horizontal; LCSC C173006
R33, R34, R35, R36, R37, R38, R39, R40: 0R39; R_Axial_DIN0614_L14.3mm_D5.7mm_P20.32mm_Horizontal; LCSC C334290
R41: 4R7; R_Axial_DIN0309_L9.0mm_D3.2mm_P12.70mm_Horizontal; LCSC C57725
R42: 4R7; R_Axial_DIN0411_L9.9mm_D3.6mm_P15.24mm_Horizontal; LCSC C138189
R43: 10k; R_Axial_DIN0309_L9.0mm_D3.2mm_P12.70mm_Horizontal; LCSC C57725
R44, R45, R46, R47, R48, R49, R50, R51: 1R; R_Axial_DIN0411_L9.9mm_D3.6mm_P15.24mm_Horizontal; LCSC C138189
R52: 100R; R_Axial_DIN0207_L6.3mm_D2.5mm_P7.62mm_Horizontal; LCSC C138189
U1: MOC3020M; DIP-6_W7.62mm

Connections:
+48V: C12.1, C13.1, C16.1, C17.1, D5.1 (K), D7.1 (K), J3.1, Q9.1 (E), Q15.2 (C), Q17.2 (C), Q19.2 (C), Q21.2 (C), Q23.2 (C), R3.2, R4.2, R13.2, R17.2, R19.2, R25.2
-48V: C5.1, C14.2, C15.1, C18.2, C19.2, C22.2, D2.1 (K), D6.2 (A), D8.2 (A), J2.2, Q16.2 (C), Q18.2 (C), Q20.2 (C), Q22.2 (C), Q24.2 (C), R12.1, R24.1, R28.1
BIAS1: C10.2, C21.2, C25.2, D3.2 (A), D13.1 (K), Q10.2 (C), Q11.2 (C), Q15.1 (B), R21.2, U1.6
BIAS2: C10.1, C21.1, D4.1 (K), D14.2 (A), Q11.3 (E), Q12.2 (C), Q16.1 (B), R23.1, U1.4
GND: C11.1, C12.2, C13.2, C14.1, C15.2, C16.2, C17.2, C18.1, C19.1, D9.2 (A), D10.1 (K), D11.2 (A), D12.1 (K), J1.2, J2.1, J3.2, JP1.1, R20.2, R43.1
GNDS: C2.1, C4.1, C8.1, C23.1, C24.2, D1.2 (A), D11.1 (K), D12.2 (A), J8.2, J9.2 (Ext), JP2.1, Q8.3 (C), R2.2, R16.2, R20.1
INPUT: C1.2, J8.1, J9.1 (In)
unnamed: C1.1, R1.2, R2.1
unnamed: C2.2, Q1.2 (B), R1.1
unnamed: C3.1, R5.2
unnamed: C3.2, Q3.2 (B), Q4.2 (B), Q4.3 (C), Q6.3 (C)
unnamed: C4.2, D1.1 (K), Q5.2 (B), Q6.2 (B), R13.1
unnamed: C6.1, Q2.2 (B), R14.2, R15.2
unnamed: C7.2, C8.2
unnamed: C11.2, R41.1
unnamed: C9.1, C20.1, Q3.3 (C), Q5.3 (C), Q8.2 (B), Q9.3 (C), R5.1
unnamed: C6.2, C20.2, D5.2 (A), D6.1 (K), D13.2 (A), D14.1 (K), L1.2, Q13.1 (E), Q14.1 (E), R14.1, R26.2, R27.1, R31.1, R32.2, R33.1, R34.2, R35.1, R36.2, R37.1, R38.2, R39.1, R40.2, R41.2, R42.1, R43.2
unnamed: C5.2, C22.1, D2.2 (A), Q7.2 (B), Q12.1 (B), R16.1
unnamed: C7.1, C23.2, R15.1
unnamed: C24.1, R18.2
unnamed: C9.2, C25.1, R18.1
unnamed: D3.1 (K), Q13.3 (C)
unnamed: D4.2 (A), Q14.3 (C)
unnamed: D7.2 (A), D9.1 (K)
unnamed: D8.1 (K), D10.2 (A)
unnamed: J4.1, JP1.2
unnamed: J6.1, JP2.2
unnamed: Q1.1 (E), R6.2
unnamed: Q1.3 (C), Q5.1 (E)
unnamed: Q2.1 (E), R7.2
unnamed: Q2.3 (C), Q6.1 (E)
unnamed: Q3.1 (E), R3.1
unnamed: Q4.1 (E), R4.1
unnamed: Q7.1 (E), R12.2
unnamed: Q7.3 (C), R11.1
unnamed: Q8.1 (E), Q10.1 (B), R17.1
unnamed: Q9.2 (B), Q10.3 (E), R19.1
unnamed: Q11.1 (B), R21.1, R22.3
unnamed: Q12.3 (E), R24.2
unnamed: Q13.2 (B), R25.1, R26.1, R29.1
unnamed: Q14.2 (B), R27.2, R28.2, R30.1
unnamed: Q15.3 (E), R31.2, R44.1, R45.1, R46.1, R47.1
unnamed: Q16.3 (E), R32.1, R48.1, R49.1, R50.1, R51.1
unnamed: Q17.1 (B), R47.2
unnamed: Q17.3 (E), R33.2
unnamed: Q18.1 (B), R48.2
unnamed: Q18.3 (E), R34.1
unnamed: Q19.1 (B), R46.2
unnamed: Q19.3 (E), R35.2
unnamed: Q20.1 (B), R49.2
unnamed: Q20.3 (E), R36.1
unnamed: Q21.1 (B), R45.2
unnamed: Q21.3 (E), R37.2
unnamed: Q22.1 (B), R50.2
unnamed: Q22.3 (E), R38.1
unnamed: Q23.1 (B), R44.2
unnamed: Q23.3 (E), R29.2, R39.2, R52.2
unnamed: Q24.1 (B), R51.2
unnamed: Q24.3 (E), R30.2, R40.1, U1.2
unnamed: R7.1, R9.2, R10.1
unnamed: R8.1, R9.1, R10.2, R11.2
unnamed: R6.1, R8.2, R10.3
unnamed: R22.1, R22.2, R23.2
unnamed: R52.1, U1.1
OUTPUT: J1.1, L1.1, R42.2

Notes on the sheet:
c300 Designed by Michael Chua (AmpsLab) PCB and modifications by Daniel Marks CC-BY-SA 4.0

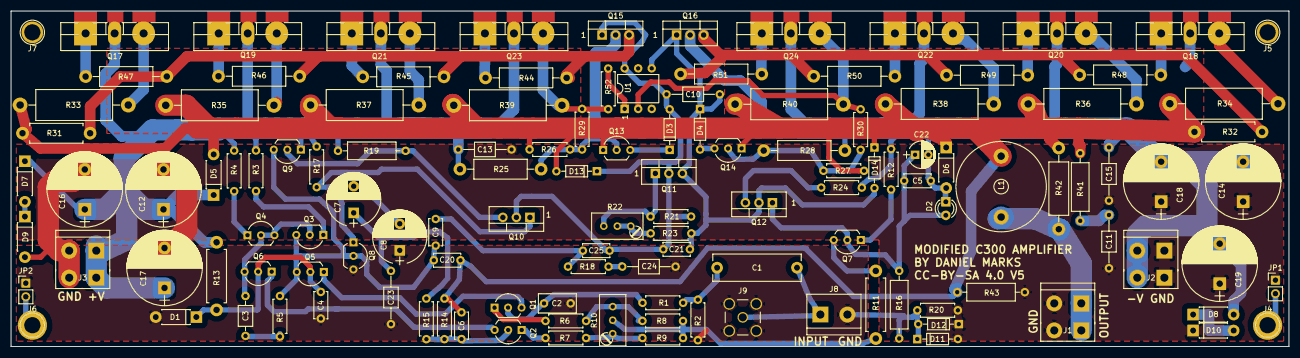
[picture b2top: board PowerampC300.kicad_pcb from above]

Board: 2 copper layers, 240.0 x 63.0 mm, 128 parts (0 on the bottom side), 65 nets.

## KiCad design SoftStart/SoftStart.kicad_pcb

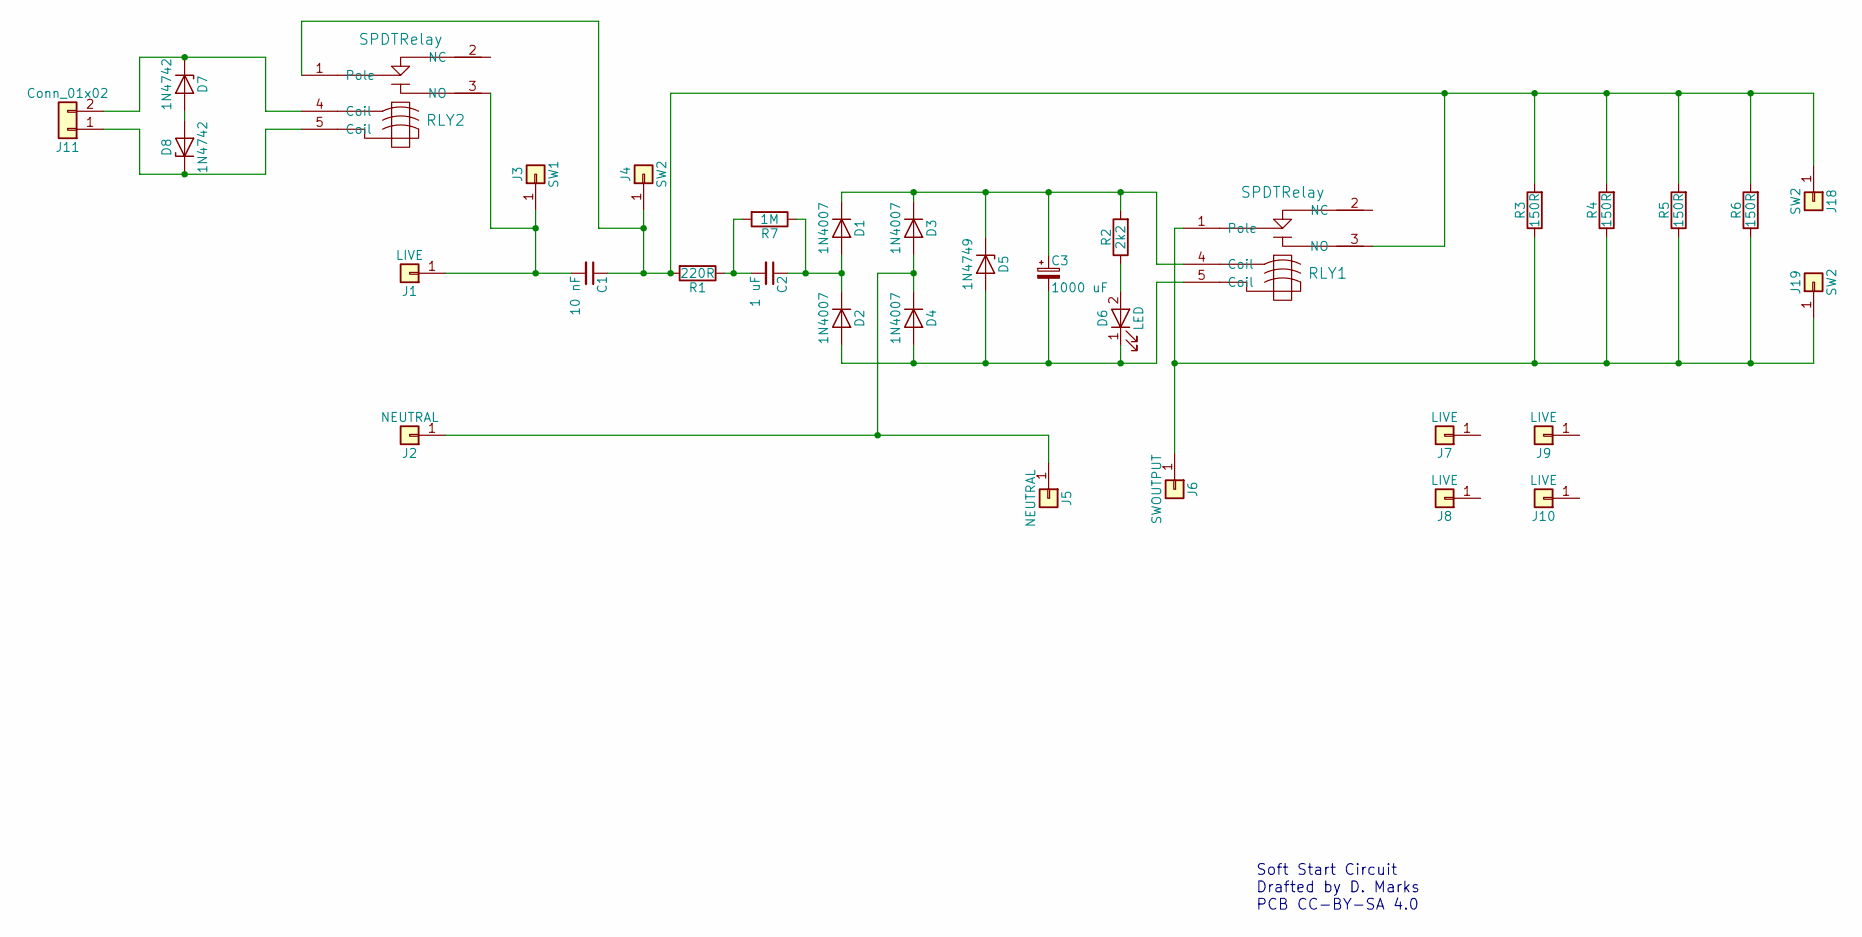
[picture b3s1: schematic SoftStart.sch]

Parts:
C1: 10 nF; C_Rect_L11.5mm_W4.5mm_P10.00mm_MKT; LCSC C342770
C2: 1 uF; C_Rect_L24.0mm_W10.1mm_P22.50mm_MKT; LCSC C390065
C3: 1000 uF; CP_Radial_D10.0mm_P5.00mm; LCSC C338226
D1, D2, D3, D4: 1N4007; D_DO-41_SOD81_P7.62mm_Horizontal; LCSC C193790
D5: 1N4749; D_DO-41_SOD81_P7.62mm_Horizontal; LCSC C2552
D6: LED; LED_D3.0mm; LCSC C99771
D7, D8: 1N4742; D_DO-41_SOD81_P7.62mm_Horizontal; LCSC C2552
J1: LIVE; SpadeTerminal635
J2, J5: NEUTRAL; SpadeTerminal635
J3: SW1; SpadeTerminal635
J4, J18, J19: SW2; SpadeTerminal635
J6: SWOUTPUT; SpadeTerminal635
J7, J8, J9, J10: LIVE; 1pin
J11: Conn_01x02; TerminalBlock_bornier-2_P5.08mm
R1: 220R; R_Axial_Power_L20.0mm_W6.4mm_P22.40mm; LCSC C334296
R2: 2k2; R_Axial_DIN0207_L6.3mm_D2.5mm_P7.62mm_Horizontal; LCSC C58595
R3, R4, R5, R6: 150R; R_Axial_Power_L20.0mm_W6.4mm_P22.40mm; LCSC C334292
R7: 1M; R_Axial_DIN0207_L6.3mm_D2.5mm_P7.62mm_Horizontal; LCSC C334296
RLY1, RLY2: SPDTRelay; SMIHRelay; LCSC C133339

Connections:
unnamed: C1.1, J4.1, J18.1, R1.2, R3.2, R4.2, R5.2, R6.2, RLY1.3 (NO), RLY2.1 (Pole)
unnamed: C1.2, J1.1, J3.1, RLY2.3 (NO)
unnamed: C2.1, D1.2 (A), D2.1 (K), R7.1
unnamed: C2.2, R1.1, R7.2
unnamed: C3.1, D1.1 (K), D3.1 (K), D5.1 (K), R2.2, RLY1.4 (Coil)
unnamed: C3.2, D2.2 (A), D4.2 (A), D5.2 (A), D6.1 (K), RLY1.5 (Coil)
unnamed: D3.2 (A), D4.1 (K), J2.1, J5.1
unnamed: D6.2 (A), R2.1
unnamed: D7.1 (K), J11.2, RLY2.4 (Coil)
unnamed: D7.2 (A), D8.2 (A)
unnamed: D8.1 (K), J11.1, RLY2.5 (Coil)
unnamed: J6.1, J19.1, R3.1, R4.1, R5.1, R6.1, RLY1.1 (Pole)

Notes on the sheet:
Soft Start Circuit Drafted by D. Marks PCB CC-BY-SA 4.0

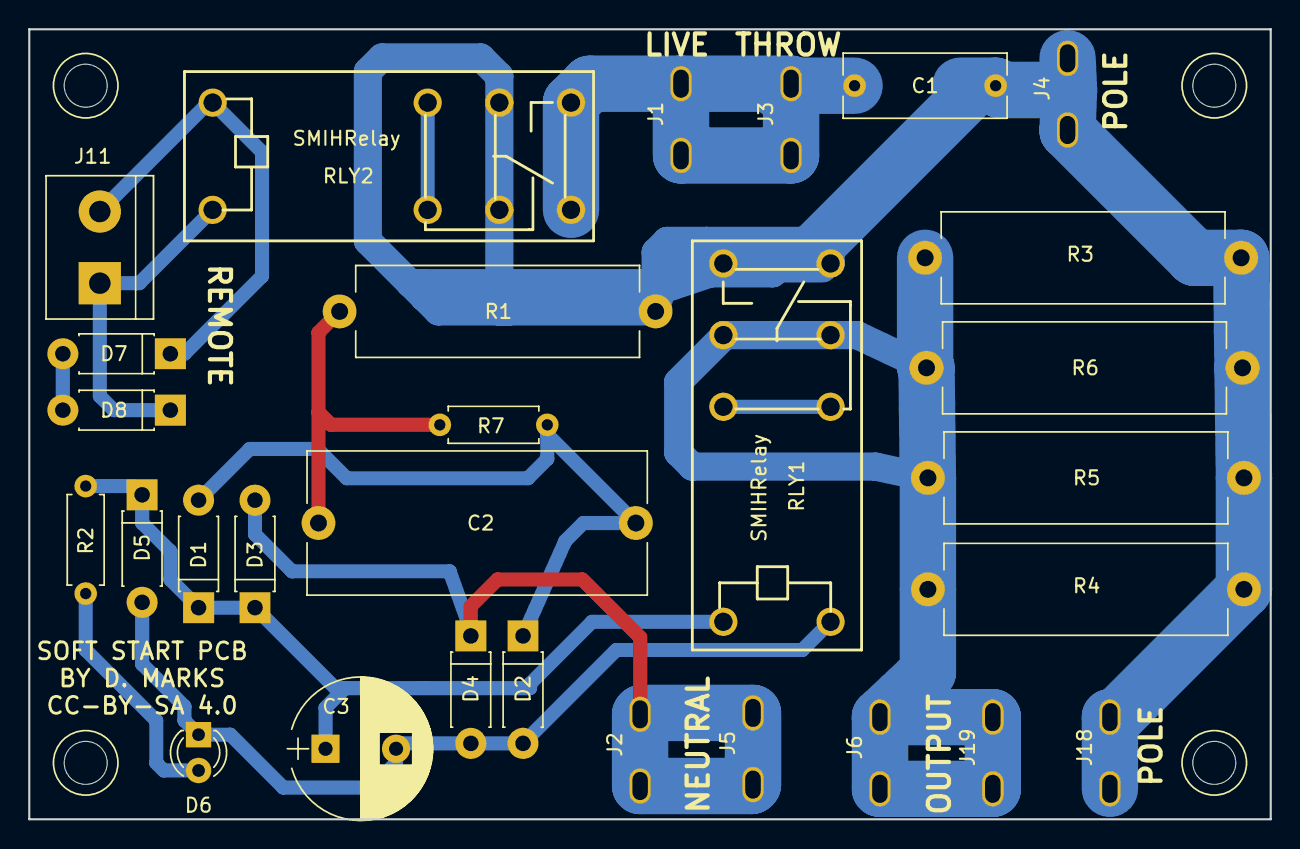
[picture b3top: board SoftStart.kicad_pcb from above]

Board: 2 copper layers, 88.0 x 56.0 mm, 33 parts (0 on the bottom side), 12 nets.

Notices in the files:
PowerCond/PowerCond.kicad_pcb:
BY D MARKS CC-BY-SA 4.0
PowerampC300/PowerampC300.kicad_pcb:
CC-BY-SA 4.0 V5
XLRtoBal/XLRtoBal.kicad_pcb:
PCB BY DANIEL MARKS CC-BY-SA 4.0
